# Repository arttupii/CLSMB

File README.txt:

Closed loop step motor controller

Two modes are supported. Step loss compensation and load position control mode.
You can select mode from config.h file.
     
    Architecture of closed loop step motor controller:

                                             +---------+--------+
                        +---------------+    | Rotary  |  Step  |
                        |               |    | encoder |  Motor |
                        |               |    |         |        |
                        |               |    |         |        |
           stepIn------>|D8             |    |         |        |
                        |   Arduino     |    |         |        |
           dirIn------->|D9 Nano        |    |  A   B  |        |
                        |               |    +---------+--------+
           EnIn-------->|D10            |       |   |     ^^^^
                        |               |IN_A   |   |     ||||
           LED---------<|D13          D2|<------+   |     ||||
                        |               |           |     ||||
        _________       |               |IN_B       |     ||||
        FEED HOLD------<|D7           D3|<----------+     ||||
                        |               |                 ||||
                        |  A2  A1  A0   |                 ||||
                        +---------------+                 ||||
                           |   |   |                      ||||
                           |   |   |                      ||||
                           V   V   V                      ||||
                        +---------------+                 ||||
                        | !EN DIR  STEP |                 ||||
                        |               |                 ||||
                        |  Standard    A|-----red---------+|||
                        |              _|                  ||| 
                        |  Stepmotor   A|-----blue---------+||
                        |               |                   ||  
                        |  controller  B|-----green---------+|
                        |              _|                    |
                        |  e.g. TB6600 B|-----black----------+
                        |               |
                        |               |
                        +---------------+                   

Block diagram (STEP_LOSS_COMPENSATION-mode)
                   +----------------------------------+  
                   |   +----------+                   |  
 Input(Step,En,Dir)|   | Input    |                   |                                             
 ------------------+-->| counter  |                   |                                                  
                       |          |                   |              +--------------+       +--------------+
                   +---|          |                   |              |              |       | Step Motor   |
                   |   +----------+                   V    (Switch)  | Step         |       |              |
                   |                                  +----O         | Motor        |------>|              |
                   |   +----------+   +----------+         ------O-->| Driver       |       |              |
                   +-->|Deviation |   |          |    +----O  ^      | (e.g TB6600) |       |              |
                       |counter   |-->| >n steps |    ^       |      |              |       |              |
                   +-->|          |   |          |    |       |      +--------------+       +--------------+
                   |   +----------+   +---------+     |       |                             | Rotary       |
                   |                        |         |       |                             | encorer      |
                   |                        V         |       |                             |              |
                   |   +----------+      +----------------+   |                             |              |
                   +---|Rotation  |      |                |   |                             +--------------+
                       |position  |      | Fix position   |   |                                    |
                       |counter   |      | (Generate      |---+                                    |     
                   +-->|          |      |step,dir pulses)|                                        |     
                   |   +----------+      +----------------+                                        |     
                   |                                                                               |  
                   +-------------------------------------------------------------------------------+

Block diagram (LOAD_POSITION_CONTROL-mode)
                                                         
                       +----------+                      
 Input(Step,En,Dir)    | Input    |                                                                 
 --------------------->| counter  |                                                                      
                       |          |                                  +--------------+       +--------------+
                   +---|          |                                  |              |       | Step Motor   |
                   |   +----------+                                  | Step         |       |              |
                   |                                                 | Motor        |------>|              |
                   |   +----------+   +----------+    +------------->| Driver       |       |              |
                   +-->|Deviation |   |          |    |              | (e.g TB6600) |       |              |
                       |counter   |-->| >n steps |    |              |              |       |              |
                   +-->|          |   |          |    |              +--------------+       +--------------+
                   |   +----------+   +---------+     |                                     | Rotary       |
                   |                        |         |                                     | encorer      |
                   |                        V         |                                     |              |
                   |   +----------+      +----------------+                                 |              |
                   +---|Rotation  |      |                |                                 +--------------+
                       |position  |      | Fix position   |                                        |
                       |counter   |      | (Generate      |                                        |     
                   +-->|          |      |step,dir pulses)|                                        |     
                   |   +----------+      +----------------+                                        |     
                   |                                                                               |  
                   +-------------------------------------------------------------------------------+

The modes explained: https://www.linearmotiontips.com/how-does-closed-loop-stepper-control-work/
                                    
Hox!
 - Because of speed optimizations you cannot change pinout without code changes. 
 - FEED HOLD is open collector output. With this pin you can ask "feed hold" from CNC machine controller
        steps loss --> FEED HOLD is LOW.
        normally ---> FEED HOLD is open
 - LOAD_POSITION_CONTROL mode needs something. "Direct control" causes too much vibrations. 
 - STEP_LOSS_COMPENSATION mode works
 
List of Known Bugs:
 - You should swap D3 and D8 pins on Arduino nano (this needs also some code changes). StepIn needs RISING interrupt. CHANGE interrupt causes too many interrupts for arduino nano and it cannot handle all of them. This issue has been fixed in ESP2866 branch.

 Compatible with:
     * Arduino nano and Arduino Pro Mini 
     * a standard step motor controller (e.g. a4988 and TB6600)
     * a standard rotary incremental encoder (e.g HN3806-AB-400N, AS5040 or similar)
               +---+   +---+   +---+   +---+
            A -+   +---+   +---+   +---+

              ---+   +---+   +---+   +---+  
            B    +---+   +---+   +---+   +--
     * NEMA xx Stepper motor
 
Demo video: 
https://youtu.be/jLogS5AQ-yQ (AS5040 encoder and A4988 step motor controller)
https://youtu.be/jxansaLNb5I (Serial Plotter view. #define ENABLE_PRINTS 100)

Useful links:
https://www.banggood.com/NANO-IO-Shield-Expansion-Board-Nano-V3-Improved-Version-No-Cable-For-Arduino-p-1010994.html?rmmds=search&cur_warehouse=CN
https://www.banggood.com/TB6600-Upgraded-Stepper-Motor-Driver-Controller-for-4A-940V-TTL-32-Micro-Step-2-or-4-Phase-of-4257-Stepper-Motor-3D-Printer-CNC-Part-p-1453122.html?rmmds=search&cur_warehouse=CN
https://www.banggood.com/3D-Printer-42-Stepper-Motor-Drive-Expansion-Board-8825-A4988-p-1028319.html?rmmds=search&cur_warehouse=CN
https://www.banggood.com/Geeetech-Stepper-Driver-A4988-With-Heatsink-And-Sticker-For-3D-Printer-p-1229214.html?rmmds=search&cur_warehouse=CN

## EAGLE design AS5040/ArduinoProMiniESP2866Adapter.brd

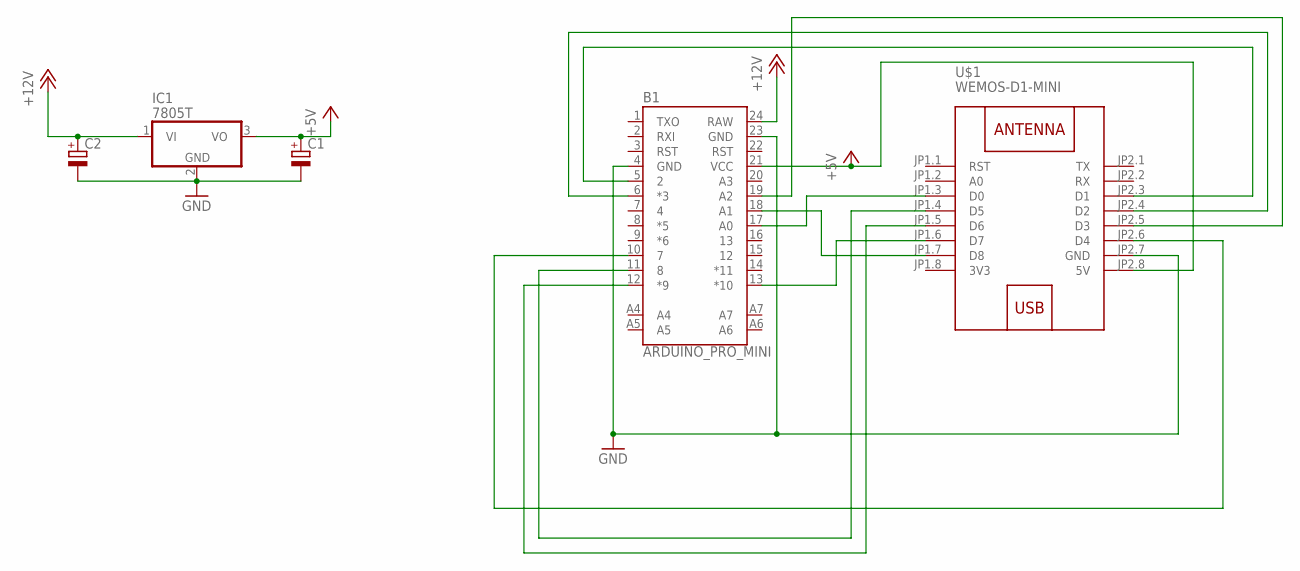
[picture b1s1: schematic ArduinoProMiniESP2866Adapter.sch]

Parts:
B1: ARDUINO_PRO_MINI
C1, C2: CPOL-EUE2-4; E2-4
IC1: 7805T; TO220H
U$1: WEMOS-D1-MINI

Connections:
3V3: U$1.JP1.8 (3V3)
+5V: B1.21 (VCC), C1.+, IC1.3 (VO), U$1.JP2.8 (5V)
+12V: B1.24 (RAW), C2.+, IC1.1 (VI)
GND: B1.4 (GND), B1.23 (GND), C1.-, C2.-, IC1.2 (GND), U$1.JP2.7 (GND)
unnamed: B1.11 (8), U$1.JP1.4 (D5)
unnamed: B1.12 (*9), U$1.JP1.5 (D6)
unnamed: B1.13 (*10), U$1.JP1.6 (D7)
unnamed: B1.5 (2), U$1.JP2.3 (D1)
unnamed: B1.6 (*3), U$1.JP2.4 (D2)
unnamed: B1.19 (A2), U$1.JP2.5 (D3)
unnamed: B1.18 (A1), U$1.JP1.7 (D8)
unnamed: B1.17 (A0), U$1.JP1.3 (D0)
unnamed: B1.10 (7), U$1.JP2.6 (D4)

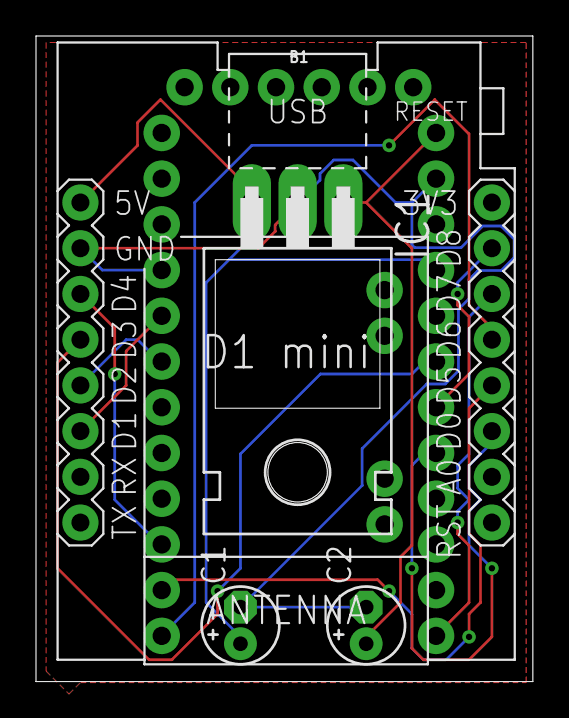
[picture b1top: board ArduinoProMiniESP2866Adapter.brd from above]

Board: 2 copper layers, 27.6 x 35.9 mm, 5 parts (0 on the bottom side), 12 nets.

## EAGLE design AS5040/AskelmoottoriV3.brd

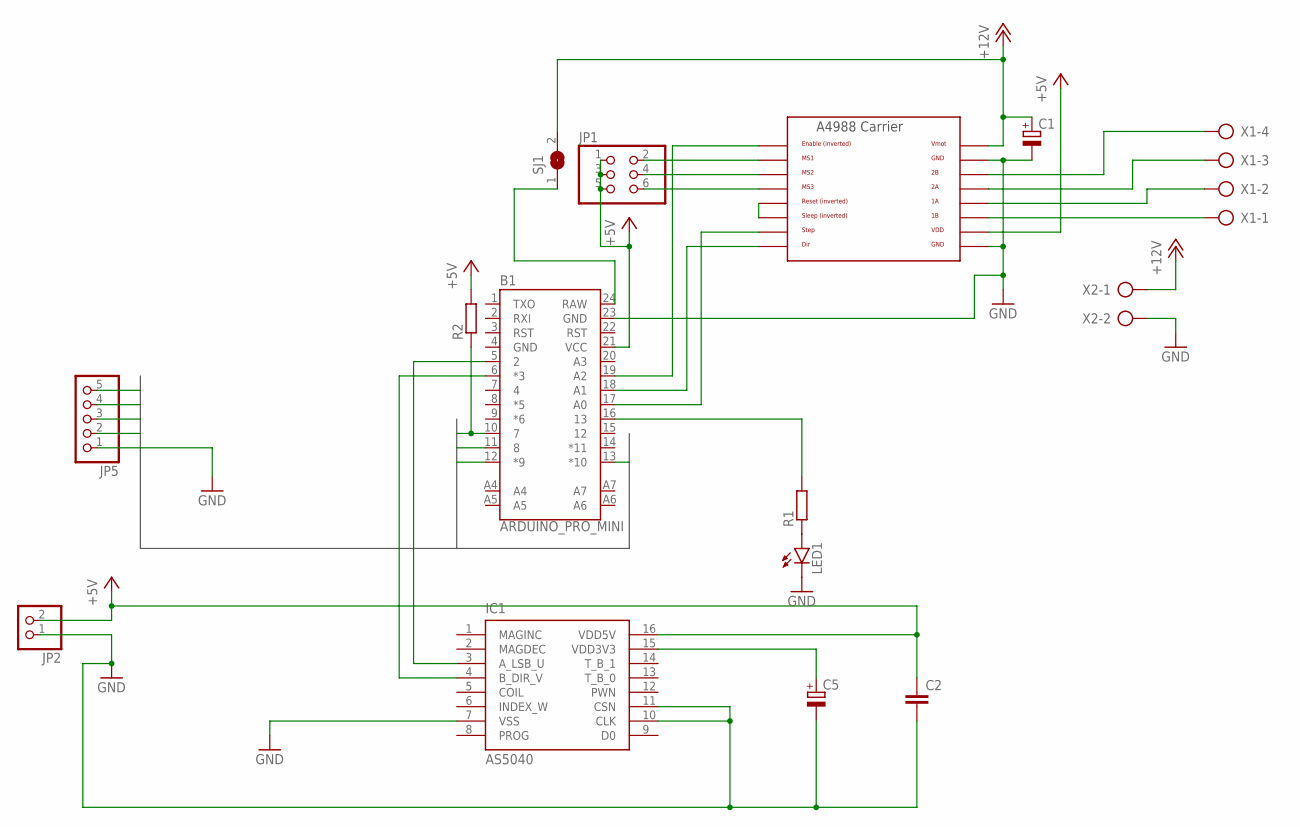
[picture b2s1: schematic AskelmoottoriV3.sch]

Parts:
B1: ARDUINO_PRO_MINI
C1: CPOL-EUE5-8.5; E5-8,5
C2: C-EU025-030X050; C025-030X050
C5: CPOL-EUE2.5-5; E2,5-5
IC1: AS5040; SSOP16
JP1: PINHD-2X3; 2X03
JP2: PINHD-1X2; 1X02
JP5: PINHD-1X5; 1X05
LED1: LED3MM
R1, R2: R-EU_0207/10; 0207/10
SJ1: SJ
U$1: A4988BREAKOUT
X1: AK300/4
X2: AK300/2

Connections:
+5V: B1.21 (VCC), C2.1, IC1.16 (VDD5V), JP1.1, JP1.3, JP1.5, JP2.2, R2.2, U$1.VDD
+12V: C1.+, SJ1.2, U$1.VMOT, X2.1
DIR: B1.12 (*9), JP5.3
EN: B1.13 (*10), JP5.4
FEED_HOLD: B1.10 (7), JP5.5, R2.1
GND: B1.4 (GND), B1.23 (GND), C1.-, C2.2, C5.-, IC1.7 (VSS), IC1.10 (CLK), IC1.11 (CSN), JP2.1, JP5.1, LED1.K (C), U$1.GND, U$1.GND@0 (GND), X2.2
unnamed: U$1.2B, X1.4
unnamed: U$1.2A, X1.3
unnamed: U$1.1A, X1.2
unnamed: U$1.1B, X1.1
unnamed: B1.6 (*3), IC1.4 (B_DIR_V)
unnamed: B1.16 (13), R1.2
unnamed: B1.17 (A0), U$1.STEP
unnamed: B1.18 (A1), U$1.DIR
unnamed: B1.19 (A2), U$1.EN
unnamed: U$1.RST, U$1.SLP (SLEEP)
unnamed: JP1.2, U$1.MS1
unnamed: JP1.4, U$1.MS2
unnamed: B1.24 (RAW), SJ1.1
unnamed: C5.+, IC1.15 (VDD3V3)
unnamed: JP1.6, U$1.MS3
unnamed: B1.5 (2), IC1.3 (A_LSB_U)
unnamed: LED1.A, R1.1
STEP: B1.11 (8), JP5.2

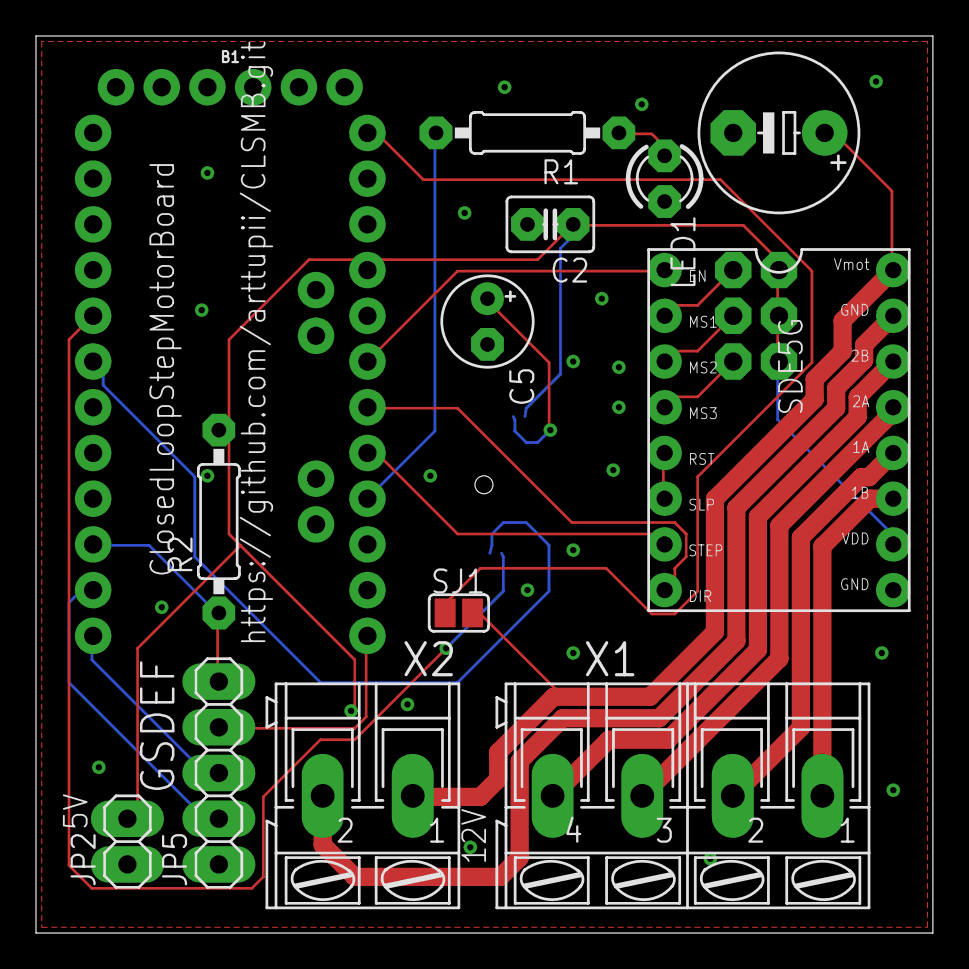
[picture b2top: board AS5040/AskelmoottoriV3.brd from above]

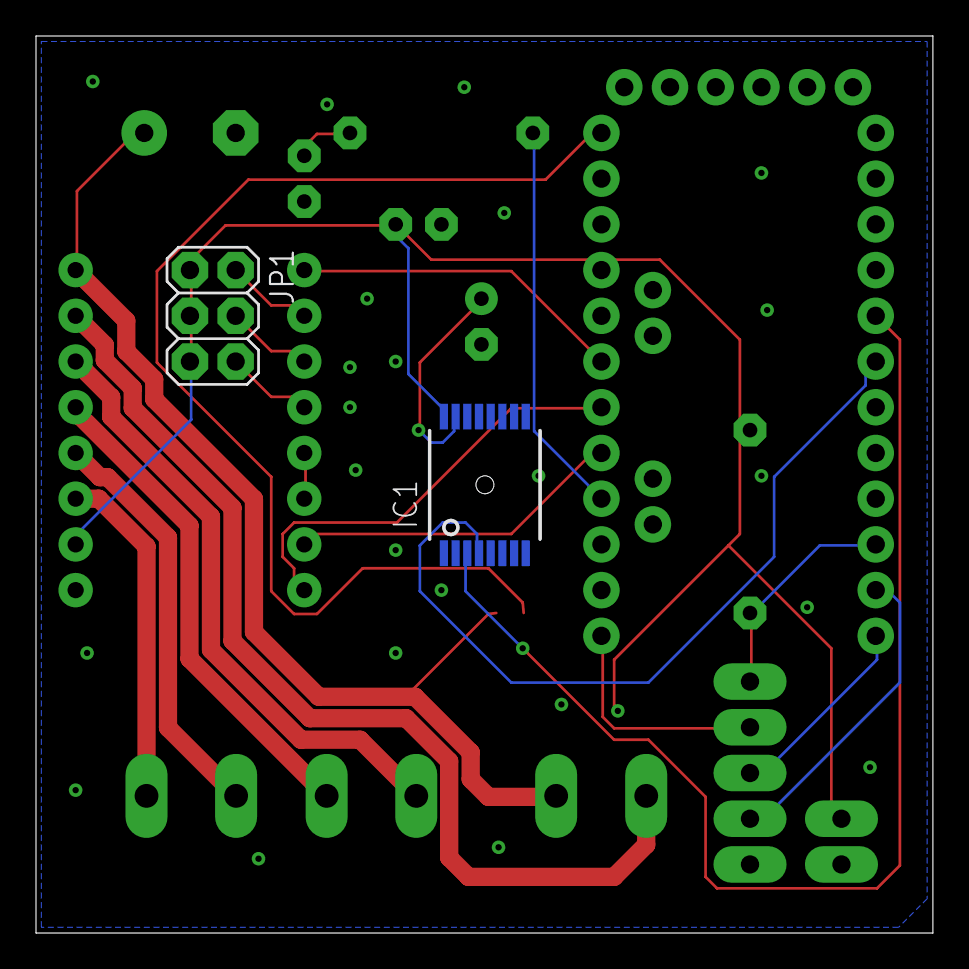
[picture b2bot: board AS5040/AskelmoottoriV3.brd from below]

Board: 2 copper layers, 49.8 x 49.8 mm, 15 parts (2 on the bottom side), 24 nets.

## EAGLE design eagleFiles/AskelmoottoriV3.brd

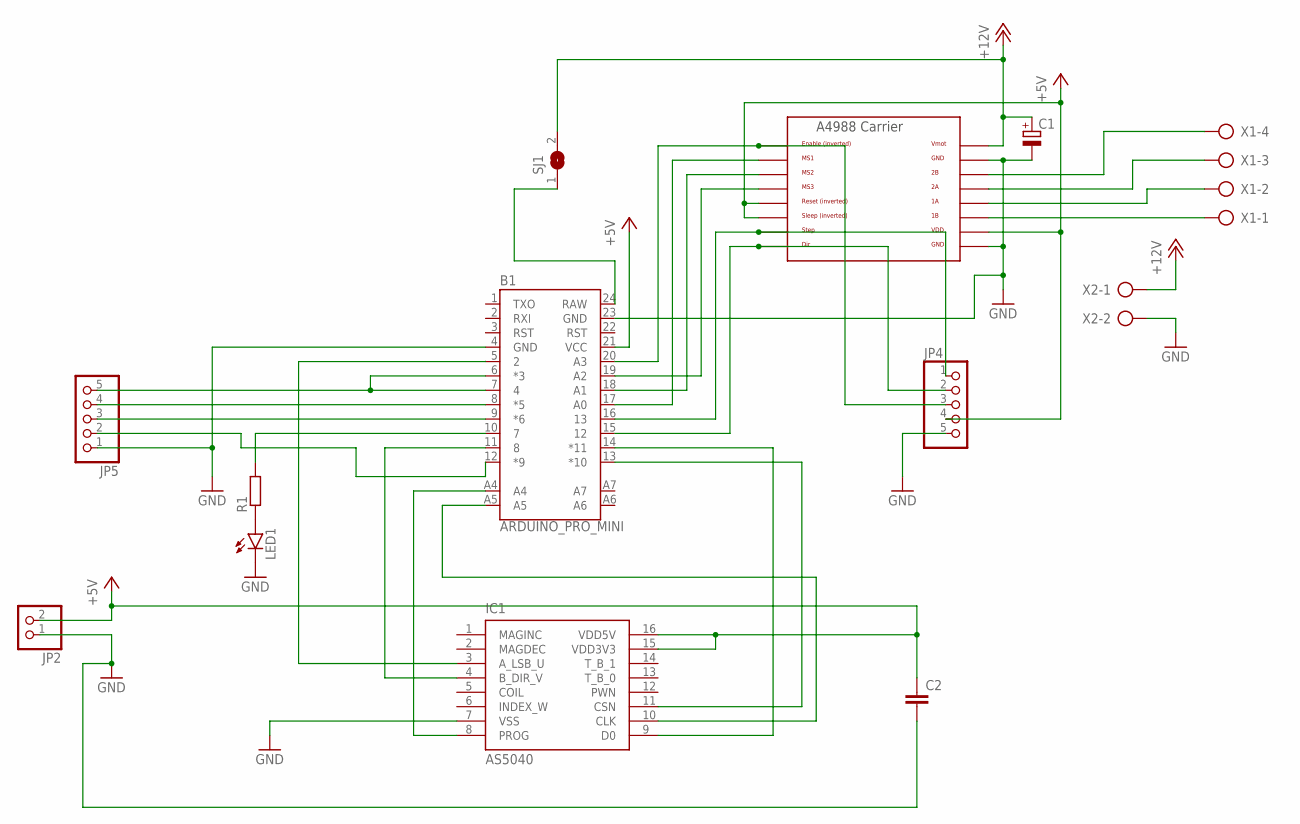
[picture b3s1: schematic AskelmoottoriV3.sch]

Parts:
B1: ARDUINO_PRO_MINI
C1: CPOL-EUE5-8.5; E5-8,5
C2: C-EU025-030X050; C025-030X050
IC1: AS5040; SSOP16
JP2: PINHD-1X2; 1X02
JP4, JP5: PINHD-1X5; 1X05
LED1: LED3MM
R1: R-EU_0207/10; 0207/10
SJ1: SJ
U$1: A4988BREAKOUT
X1: AK300/4
X2: AK300/2

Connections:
+5V: B1.21 (VCC), C2.1, IC1.15 (VDD3V3), IC1.16 (VDD5V), JP2.2, JP4.4, U$1.RST, U$1.SLP (SLEEP), U$1.VDD
+12V: C1.+, SJ1.2, U$1.VMOT, X2.1
GND: B1.4 (GND), B1.23 (GND), C1.-, C2.2, IC1.7 (VSS), JP2.1, JP4.5, JP5.1, LED1.K (C), U$1.GND, U$1.GND@0 (GND), X2.2
unnamed: U$1.2B, X1.4
unnamed: U$1.2A, X1.3
unnamed: U$1.1A, X1.2
unnamed: U$1.1B, X1.1
unnamed: B1.17 (A0), U$1.MS1
unnamed: B1.18 (A1), U$1.MS2
unnamed: B1.19 (A2), U$1.MS3
unnamed: B1.20 (A3), JP4.3, U$1.EN
unnamed: B1.5 (2), IC1.3 (A_LSB_U)
unnamed: B1.16 (13), JP4.1, U$1.STEP
unnamed: B1.15 (12), JP4.2, U$1.DIR
unnamed: B1.11 (8), IC1.4 (B_DIR_V)
unnamed: B1.6 (*3), B1.7 (4), JP5.5
unnamed: B1.24 (RAW), SJ1.1
unnamed: B1.A5, IC1.10 (CLK)
unnamed: B1.A4, IC1.8 (PROG)
unnamed: B1.13 (*10), IC1.11 (CSN)
unnamed: B1.8 (*5), JP5.4
unnamed: B1.9 (*6), JP5.3
unnamed: LED1.A, R1.1
unnamed: B1.10 (7), R1.2
unnamed: B1.12 (*9), JP5.2
unnamed: B1.14 (*11), IC1.9 (D0)

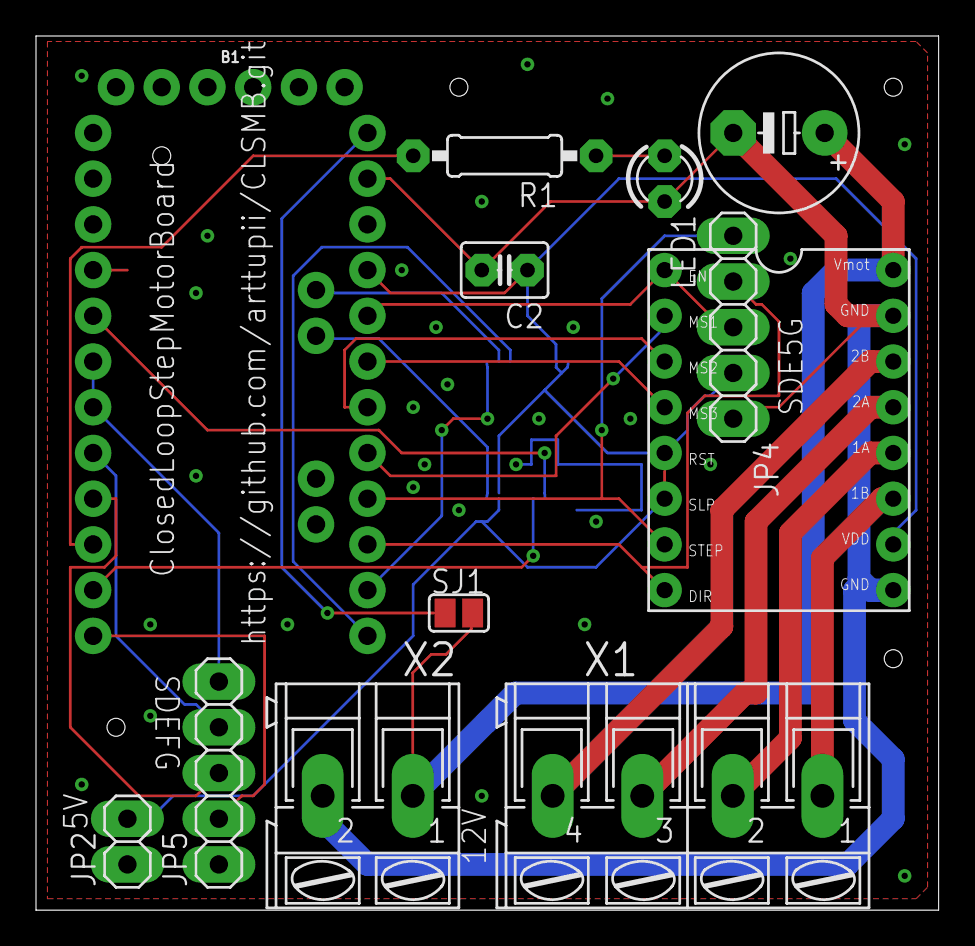
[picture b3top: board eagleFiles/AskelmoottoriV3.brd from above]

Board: 2 copper layers, 50.1 x 48.6 mm, 13 parts (1 on the bottom side), 26 nets.

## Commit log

2019-05-10 draft
2019-06-21 Add schematic&gerber files + README
2019-06-22 Removed IN_STEP1 define
2019-06-24 Untested quadrature signal support
2019-06-25 Updated pinout
2019-06-26 Speed optimizations
2019-06-26 Removed eagle&photo files
2019-06-26 FEED HOLD pin
2019-06-26 Fixes
2019-06-26 Fix bug
2019-06-27 AS5040 board&Schematic files
2019-06-27 Demo code
2019-06-27 FLIP_ENCODER flag
2019-06-27 Add debug prints
2019-06-27 Send step difference to serial plotter
2019-06-27 Create LICENSE
2019-06-27 Improve debug prints
2019-06-29 Improve code
2019-06-29 Fix revolutions/second calculation
2019-06-30 Rename ENCODER_PPR to ENCODER_STATE_CHANGE_PER_REV
2019-07-01 Remove unused value
2019-07-01 Update eagle files
2019-07-01 Improve main loop
2019-07-01 Fixed bugs
2019-07-02 Add crosshair
2019-07-03 Gerber files
2019-07-05 Backup
2019-07-05 Run step motor in ISR(TIMER2_OVF_vect)
2019-07-05 Remove dependency to Millis()
2019-07-06 Add STEP_LOSS_COMPENSATION & LOAD_POSITION_CONTROL modes
2019-07-06 Improve LOAD_POSITION_CONTROL_MODE
2019-07-07 Small fixes
2019-07-11 Add support for HN3806-AB-400N. Optimize performance
2019-07-11 Add quadrature encoding X1, X2 and X3 modes
2019-09-08 ESP2866 support
2022-05-28 Update StepMotorLoop.ino
    Remove dependency to myEspNowMeshConfig.h

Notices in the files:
parts and their libraries:
SparkFun-Boards: Licensing: Creative Commons ShareAlike 4.0 International - https://creativecommons.org/licenses/by-sa/4.0
diy-modules: Released under the Creative Commons Attribution 4.0 International License: http://creativecommons.org/licenses/by/4.0
